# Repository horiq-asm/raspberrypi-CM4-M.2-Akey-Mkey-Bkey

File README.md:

boot CM5 via NVMe behind PCIe switch !!!<br>
新たに入手したCM5を入れるとNVMeからbootできました。
2024年12月クリスマスプレゼントです。<br>
youtube で動作画像ご覧ください　https://youtu.be/MDhNWYu6bRE

# raspberrypi-CM4-M.2-Akey-Mkey-Bkey
raspberypi　CM4にpcie swich を載せてM.2基板を複数動作できる基板を作成しました。
wifi6　１G　2.5Gのnicが動きます。
MkeyにはNVMeを搭載しています。

$ lspci<br>
00:00.0 PCI bridge: Broadcom Inc. and subsidiaries BCM2711 PCIe Bridge (rev 20)<br>
01:00.0 PCI bridge: ASMedia Technology Inc. ASM1184e 4-Port PCIe x1 Gen2 Packet Switch<br>
02:01.0 PCI bridge: ASMedia Technology Inc. ASM1184e 4-Port PCIe x1 Gen2 Packet Switch<br>
02:03.0 PCI bridge: ASMedia Technology Inc. ASM1184e 4-Port PCIe x1 Gen2 Packet Switch<br>
02:05.0 PCI bridge: ASMedia Technology Inc. ASM1184e 4-Port PCIe x1 Gen2 Packet Switch<br>
02:07.0 PCI bridge: ASMedia Technology Inc. ASM1184e 4-Port PCIe x1 Gen2 Packet Switch<br>
03:00.0 Network controller: MEDIATEK Corp. MT7921 802.11ax PCI Express Wireless Network Adapter<br>
04:00.0 Non-Volatile memory controller: KIOXIA Corporation NVMe SSD (rev 01)<br>
05:00.0 Ethernet controller: Intel Corporation Ethernet Controller I226-V (rev 04)<br>
<br>
$ ethtool eth1<br>
Settings for eth1:<br>
        Supported ports: [ TP ]<br>
        Supported link modes:   10baseT/Half 10baseT/Full<br>
                                100baseT/Half 100baseT/Full<br>
                                1000baseT/Full<br>
                                2500baseT/Full<br>
        Supported pause frame use: Symmetric<br>
        Supports auto-negotiation: Yes<br>
        Supported FEC modes: Not reported<br>
        Advertised link modes:  10baseT/Half 10baseT/Full<br>
                                100baseT/Half 100baseT/Full<br>
                                1000baseT/Full<br>
                                2500baseT/Full<br>
        Advertised pause frame use: Symmetric<br>
        Advertised auto-negotiation: Yes<br>
        Advertised FEC modes: Not reported<br>
        Speed: 2500Mb/s<br>
        Duplex: Full<br>
        Auto-negotiation: on<br>
        Port: Twisted Pair<br>
        PHYAD: 0<br>
        Transceiver: internal<br>
        MDI-X: off (auto)<br>
netlink error: Operation not permitted<br>
        Current message level: 0x00000007 (7)<br>
                               drv probe link<br>
        Link detected: yes<br>
<br>
<br>
$ nmcli d s<br>
DEVICE         TYPE      STATE                   CONNECTION<br>
wlan0          wifi      connected               WIFI_AP<br>
eth1           ethernet  connected               Wired connection 2<br>
lo             loopback  connected (externally)  lo<br>
p2p-dev-wlan0  wifi-p2p  disconnected            --<br>
eth0           ethernet  unavailable             --<br>
<br>
%%%<br>
Network controller: MEDIATEK Corp. MT7921 802.11ax PCI Express Wireless Network Adapter<br>
のためには　　/boot/firmware/config.txt　　に下記の変更が必要です。<br>
[all]<br>
dtparam=pciex1<br>
dtoverlay=pcie-32bit-dma<br>
<br>
<br>
$ iw phy0 info<br>
Wiphy phy0<br>
        wiphy index: 0<br>
        max # scan SSIDs: 4<br>
        max scan IEs length: 482 bytes<br>
        max # sched scan SSIDs: 10<br>
        max # match sets: 16<br>
        Retry short limit: 7<br>
        Retry long limit: 4<br>
        Coverage class: 0 (up to 0m)<br>
        Device supports AP-side u-APSD.<br>
        Device supports T-DLS.<br>
        Supported Ciphers:<br>
                * WEP40 (00-0f-ac:1)<br>
                * WEP104 (00-0f-ac:5)<br>
                * TKIP (00-0f-ac:2)<br>
                * CCMP-128 (00-0f-ac:4)<br>
                * CCMP-256 (00-0f-ac:10)<br>
                * GCMP-128 (00-0f-ac:8)<br>
                * GCMP-256 (00-0f-ac:9)<br>
                * CMAC (00-0f-ac:6)<br>
                * CMAC-256 (00-0f-ac:13)<br>
                * GMAC-128 (00-0f-ac:11)<br>
                * GMAC-256 (00-0f-ac:12)<br>
        Available Antennas: TX 0x3 RX 0x3<br>
        Configured Antennas: TX 0x3 RX 0x3<br>
        Supported interface modes:<br>
                 * managed<br>
                 * AP<br>
                 * AP/VLAN<br>
                 * monitor<br>
                 * P2P-client<br>
                 * P2P-GO<br>
        Band 1:<br>
                Capabilities: 0x9ff<br>
                        RX LDPC<br>
                        HT20/HT40<br>
                        SM Power Save disabled<br>
                        RX Greenfield<br>
                        RX HT20 SGI<br>
                        RX HT40 SGI<br>
                        TX STBC<br>
                        RX STBC 1-stream<br>
                        Max AMSDU length: 7935 bytes<br>
                        No DSSS/CCK HT40<br>
                Maximum RX AMPDU length 65535 bytes (exponent: 0x003)<br>
                Minimum RX AMPDU time spacing: No restriction (0x00)<br>
                HT TX/RX MCS rate indexes supported: 0-15<br>
                HE Iftypes: managed<br>
                        HE MAC Capabilities (0x08011a000040):<br>
                                +HTC HE Supported<br>
                                Trigger Frame MAC Padding Duration: 2<br>
                                OM Control<br>
                                Maximum A-MPDU Length Exponent: 3<br>
                                A-MSDU in A-MPDU<br>
                        HE PHY Capabilities: (0x2270ce120dc0b306423f00):<br>
                                HE40/2.4GHz<br>
                                242 tone RUs/2.4GHz<br>
                                Device Class: 1<br>
                                LDPC Coding in Payload<br>
                                HE SU PPDU with 1x HE-LTF and 0.8us GI<br>
                                NDP with 4x HE-LTF and 3.2us GI<br>
                                STBC Tx <= 80MHz<br>
                                STBC Rx <= 80MHz<br>
                                Full Bandwidth UL MU-MIMO<br>
                                Partial Bandwidth UL MU-MIMO<br>
                                DCM Max Constellation: 2<br>
                                DCM Max Constellation Rx: 2<br>
                                SU Beamformee<br>
                                Beamformee STS <= 80Mhz: 3<br>
                                Ng = 16 SU Feedback<br>
                                Ng = 16 MU Feedback<br>
                                Codebook Size SU Feedback<br>
                                Codebook Size MU Feedback<br>
                                Triggered CQI Feedback<br>
                                Partial Bandwidth Extended Range<br>
                                PPE Threshold Present<br>
                                Power Boost Factor ar<br>
                                HE SU PPDU & HE PPDU 4x HE-LTF 0.8us GI<br>
                                20MHz in 40MHz HE PPDU 2.4GHz<br>
                                DCM Max BW: 1<br>
                                Longer Than 16HE SIG-B OFDM Symbols<br>
                                Non-Triggered CQI Feedback<br>
                                TX 1024-QAM<br>
                                RX 1024-QAM<br>
                                RX Full BW SU Using HE MU PPDU with Compression SIGB<br>
                                RX Full BW SU Using HE MU PPDU with Non-Compression SIGB<br>
                        HE RX MCS and NSS set <= 80 MHz<br>
                                1 streams: MCS 0-11<br>
                                2 streams: MCS 0-11<br>
                                3 streams: not supported<br>
                                4 streams: not supported<br>
                                5 streams: not supported<br>
                                6 streams: not supported<br>
                                7 streams: not supported<br>
                                8 streams: not supported<br>
                        HE TX MCS and NSS set <= 80 MHz<br>
                                1 streams: MCS 0-11<br>
                                2 streams: MCS 0-11<br>
                                3 streams: not supported<br>
                                4 streams: not supported<br>
                                5 streams: not supported<br>
                                6 streams: not supported<br>
                                7 streams: not supported<br>
                                8 streams: not supported<br>
                        PPE Threshold 0x39 0x1c 0xc7 0x71 0x1c 0x07<br>
                EHT Iftypes: managed<br>
                        EHT MAC Capabilities (0x0000):<br>
                        EHT PHY Capabilities: (0x0000000000000000):<br>
                        EHT MCS/NSS: (0x):<br>
                        EHT bw=20 MHz, max NSS for MCS 0-7: Rx=0, Tx=0<br>
                        EHT bw=20 MHz, max NSS for MCS 8-9: Rx=0, Tx=0<br>
                        EHT bw=20 MHz, max NSS for MCS 10-11: Rx=0, Tx=0<br>
                        EHT bw=20 MHz, max NSS for MCS 12-13: Rx=0, Tx=0<br>
                HE Iftypes: AP<br>
                        HE MAC Capabilities (0x00011a081044):<br>
                                +HTC HE Supported<br>
                                BSR<br>
                                OM Control<br>
                                Maximum A-MPDU Length Exponent: 3<br>
                                BQR<br>
                                A-MSDU in A-MPDU<br>
                                OM Control UL MU Data Disable RX<br>
                        HE PHY Capabilities: (0x0220ce120000a000000c00):<br>
                                HE40/2.4GHz<br>
                                LDPC Coding in Payload<br>
                                NDP with 4x HE-LTF and 3.2us GI<br>
                                STBC Tx <= 80MHz<br>
                                STBC Rx <= 80MHz<br>
                                Full Bandwidth UL MU-MIMO<br>
                                Partial Bandwidth UL MU-MIMO<br>
                                DCM Max Constellation: 2<br>
                                DCM Max Constellation Rx: 2<br>
                                Partial Bandwidth Extended Range<br>
                                PPE Threshold Present<br>
                                TX 1024-QAM<br>
                                RX 1024-QAM<br>
                        HE RX MCS and NSS set <= 80 MHz<br>
                                1 streams: MCS 0-11<br>
                                2 streams: MCS 0-11<br>
                                3 streams: not supported<br>
                                4 streams: not supported<br>
                                5 streams: not supported<br>
                                6 streams: not supported<br>
                                7 streams: not supported<br>
                                8 streams: not supported<br>
                        HE TX MCS and NSS set <= 80 MHz<br>
                                1 streams: MCS 0-11<br>
                                2 streams: MCS 0-11<br>
                                3 streams: not supported<br>
                                4 streams: not supported<br>
                                5 streams: not supported<br>
                                6 streams: not supported<br>
                                7 streams: not supported<br>
                                8 streams: not supported<br>
                        PPE Threshold 0x39 0x1c 0xc7 0x71 0x1c 0x07<br>
                EHT Iftypes: AP<br>
                        EHT MAC Capabilities (0x0000):<br>
                        EHT PHY Capabilities: (0x0000000000000000):<br>
                        EHT MCS/NSS: (0x):<br>
                        EHT bw=20 MHz, max NSS for MCS 0-7: Rx=0, Tx=0<br>
                        EHT bw=20 MHz, max NSS for MCS 8-9: Rx=0, Tx=0<br>
                        EHT bw=20 MHz, max NSS for MCS 10-11: Rx=0, Tx=0<br>
                        EHT bw=20 MHz, max NSS for MCS 12-13: Rx=0, Tx=0<br>
                Bitrates (non-HT):<br>
                        * 1.0 Mbps (short preamble supported)<br>
                        * 2.0 Mbps (short preamble supported)<br>
                        * 5.5 Mbps (short preamble supported)<br>
                        * 11.0 Mbps (short preamble supported)<br>
                        * 6.0 Mbps<br>
                        * 9.0 Mbps<br>
                        * 12.0 Mbps<br>
                        * 18.0 Mbps<br>
                        * 24.0 Mbps<br>
                        * 36.0 Mbps<br>
                        * 48.0 Mbps<br>
                        * 54.0 Mbps<br>
                Frequencies:<br>
                        * 2412 MHz [1] (20.0 dBm)<br>
                        * 2417 MHz [2] (20.0 dBm)<br>
                        * 2422 MHz [3] (20.0 dBm)<br>
                        * 2427 MHz [4] (20.0 dBm)<br>
                        * 2432 MHz [5] (20.0 dBm)<br>
                        * 2437 MHz [6] (20.0 dBm)<br>
                        * 2442 MHz [7] (20.0 dBm)<br>
                        * 2447 MHz [8] (20.0 dBm)<br>
                        * 2452 MHz [9] (20.0 dBm)<br>
                        * 2457 MHz [10] (20.0 dBm)<br>
                        * 2462 MHz [11] (20.0 dBm)<br>
                        * 2467 MHz [12] (20.0 dBm)<br>
                        * 2472 MHz [13] (20.0 dBm)<br>
                        * 2484 MHz [14] (20.0 dBm)<br>
        Band 2:<br>
                Capabilities: 0x9ff<br>
                        RX LDPC<br>
                        HT20/HT40<br>
                        SM Power Save disabled<br>
                        RX Greenfield<br>
                        RX HT20 SGI<br>
                        RX HT40 SGI<br>
                        TX STBC<br>
                        RX STBC 1-stream<br>
                        Max AMSDU length: 7935 bytes<br>
                        No DSSS/CCK HT40<br>
                Maximum RX AMPDU length 65535 bytes (exponent: 0x003)<br>
                Minimum RX AMPDU time spacing: No restriction (0x00)<br>
                HT TX/RX MCS rate indexes supported: 0-15<br>
                VHT Capabilities (0x339071b2):<br>
                        Max MPDU length: 11454<br>
                        Supported Channel Width: neither 160 nor 80+80<br>
                        RX LDPC<br>
                        short GI (80 MHz)<br>
                        TX STBC<br>
                        SU Beamformee<br>
                        MU Beamformee<br>
                        RX antenna pattern consistency<br>
                        TX antenna pattern consistency<br>
                VHT RX MCS set:<br>
                        1 streams: MCS 0-9<br>
                        2 streams: MCS 0-9<br>
                        3 streams: not supported<br>
                        4 streams: not supported<br>
                        5 streams: not supported<br>
                        6 streams: not supported<br>
                        7 streams: not supported<br>
                        8 streams: not supported<br>
                VHT RX highest supported: 0 Mbps<br>
                VHT TX MCS set:<br>
                        1 streams: MCS 0-9<br>
                        2 streams: MCS 0-9<br>
                        3 streams: not supported<br>
                        4 streams: not supported<br>
                        5 streams: not supported<br>
                        6 streams: not supported<br>
                        7 streams: not supported<br>
                        8 streams: not supported<br>
                VHT TX highest supported: 0 Mbps<br>
                VHT extended NSS: supported<br>
                HE Iftypes: managed<br>
                        HE MAC Capabilities (0x08011a000040):<br>
                                +HTC HE Supported<br>
                                Trigger Frame MAC Padding Duration: 2<br>
                                OM Control<br>
                                Maximum A-MPDU Length Exponent: 3<br>
                                A-MSDU in A-MPDU<br>
                        HE PHY Capabilities: (0x4470ce120dc0b306423f00):<br>
                                HE40/HE80/5GHz<br>
                                242 tone RUs/5GHz<br>
                                Device Class: 1<br>
                                LDPC Coding in Payload<br>
                                HE SU PPDU with 1x HE-LTF and 0.8us GI<br>
                                NDP with 4x HE-LTF and 3.2us GI<br>
                                STBC Tx <= 80MHz<br>
                                STBC Rx <= 80MHz<br>
                                Full Bandwidth UL MU-MIMO<br>
                                Partial Bandwidth UL MU-MIMO<br>
                                DCM Max Constellation: 2<br>
                                DCM Max Constellation Rx: 2<br>
                                SU Beamformee<br>
                                Beamformee STS <= 80Mhz: 3<br>
                                Ng = 16 SU Feedback<br>
                                Ng = 16 MU Feedback<br>
                                Codebook Size SU Feedback<br>
                                Codebook Size MU Feedback<br>
                                Triggered CQI Feedback<br>
                                Partial Bandwidth Extended Range<br>
                                PPE Threshold Present<br>
                                Power Boost Factor ar<br>
                                HE SU PPDU & HE PPDU 4x HE-LTF 0.8us GI<br>
                                20MHz in 40MHz HE PPDU 2.4GHz<br>
                                DCM Max BW: 1<br>
                                Longer Than 16HE SIG-B OFDM Symbols<br>
                                Non-Triggered CQI Feedback<br>
                                TX 1024-QAM<br>
                                RX 1024-QAM<br>
                                RX Full BW SU Using HE MU PPDU with Compression SIGB<br>
                                RX Full BW SU Using HE MU PPDU with Non-Compression SIGB<br>
                        HE RX MCS and NSS set <= 80 MHz<br>
                                1 streams: MCS 0-11<br>
                                2 streams: MCS 0-11<br>
                                3 streams: not supported<br>
                                4 streams: not supported<br>
                                5 streams: not supported<br>
                                6 streams: not supported<br>
                                7 streams: not supported<br>
                                8 streams: not supported<br>
                        HE TX MCS and NSS set <= 80 MHz<br>
                                1 streams: MCS 0-11<br>
                                2 streams: MCS 0-11<br>
                                3 streams: not supported<br>
                                4 streams: not supported<br>
                                5 streams: not supported<br>
                                6 streams: not supported<br>
                                7 streams: not supported<br>
                                8 streams: not supported<br>
                        PPE Threshold 0x39 0x1c 0xc7 0x71 0x1c 0x07<br>
                EHT Iftypes: managed<br>
                        EHT MAC Capabilities (0x0000):<br>
                        EHT PHY Capabilities: (0x0000000000000000):<br>
                        EHT MCS/NSS: (0x):<br>
                        EHT bw <= 80 MHz, max NSS for MCS 8-9: Rx=0, Tx=0<br>
                        EHT bw <= 80 MHz, max NSS for MCS 10-11: Rx=0, Tx=0<br>
                        EHT bw <= 80 MHz, max NSS for MCS 12-13: Rx=0, Tx=0<br>
                HE Iftypes: AP<br>
                        HE MAC Capabilities (0x00011a081044):<br>
                                +HTC HE Supported<br>
                                BSR<br>
                                OM Control<br>
                                Maximum A-MPDU Length Exponent: 3<br>
                                BQR<br>
                                A-MSDU in A-MPDU<br>
                                OM Control UL MU Data Disable RX<br>
                        HE PHY Capabilities: (0x0420ce120000a000000c00):<br>
                                HE40/HE80/5GHz<br>
                                LDPC Coding in Payload<br>
                                NDP with 4x HE-LTF and 3.2us GI<br>
                                STBC Tx <= 80MHz<br>
                                STBC Rx <= 80MHz<br>
                                Full Bandwidth UL MU-MIMO<br>
                                Partial Bandwidth UL MU-MIMO<br>
                                DCM Max Constellation: 2<br>
                                DCM Max Constellation Rx: 2<br>
                                Partial Bandwidth Extended Range<br>
                                PPE Threshold Present<br>
                                TX 1024-QAM<br>
                                RX 1024-QAM<br>
                        HE RX MCS and NSS set <= 80 MHz<br>
                                1 streams: MCS 0-11<br>
                                2 streams: MCS 0-11<br>
                                3 streams: not supported<br>
                                4 streams: not supported<br>
                                5 streams: not supported<br>
                                6 streams: not supported<br>
                                7 streams: not supported<br>
                                8 streams: not supported<br>
                        HE TX MCS and NSS set <= 80 MHz<br>
                                1 streams: MCS 0-11<br>
                                2 streams: MCS 0-11<br>
                                3 streams: not supported<br>
                                4 streams: not supported<br>
                                5 streams: not supported<br>
                                6 streams: not supported<br>
                                7 streams: not supported<br>
                                8 streams: not supported<br>
                        PPE Threshold 0x39 0x1c 0xc7 0x71 0x1c 0x07<br>
                EHT Iftypes: AP<br>
                        EHT MAC Capabilities (0x0000):<br>
                        EHT PHY Capabilities: (0x0000000000000000):<br>
                        EHT MCS/NSS: (0x):<br>
                        EHT bw <= 80 MHz, max NSS for MCS 8-9: Rx=0, Tx=0<br>
                        EHT bw <= 80 MHz, max NSS for MCS 10-11: Rx=0, Tx=0<br>
                        EHT bw <= 80 MHz, max NSS for MCS 12-13: Rx=0, Tx=0<br>
                Bitrates (non-HT):<br>
                        * 6.0 Mbps<br>
                        * 9.0 Mbps<br>
                        * 12.0 Mbps<br>
                        * 18.0 Mbps<br>
                        * 24.0 Mbps<br>
                        * 36.0 Mbps<br>
                        * 48.0 Mbps<br>
                        * 54.0 Mbps<br>
                Frequencies:<br>
                        * 5180 MHz [36] (20.0 dBm)<br>
                        * 5200 MHz [40] (20.0 dBm)<br>
                        * 5220 MHz [44] (20.0 dBm)<br>
                        * 5240 MHz [48] (20.0 dBm)<br>
                        * 5260 MHz [52] (20.0 dBm) (radar detection)<br>
                        * 5280 MHz [56] (20.0 dBm) (radar detection)<br>
                        * 5300 MHz [60] (20.0 dBm) (radar detection)<br>
                        * 5320 MHz [64] (20.0 dBm) (radar detection)<br>
                        * 5500 MHz [100] (23.0 dBm) (radar detection)<br>
                        * 5520 MHz [104] (23.0 dBm) (radar detection)<br>
                        * 5540 MHz [108] (23.0 dBm) (radar detection)<br>
                        * 5560 MHz [112] (23.0 dBm) (radar detection)<br>
                        * 5580 MHz [116] (23.0 dBm) (radar detection)<br>
                        * 5600 MHz [120] (23.0 dBm) (radar detection)<br>
                        * 5620 MHz [124] (23.0 dBm) (radar detection)<br>
                        * 5640 MHz [128] (23.0 dBm) (radar detection)<br>
                        * 5660 MHz [132] (23.0 dBm) (radar detection)<br>
                        * 5680 MHz [136] (23.0 dBm) (radar detection)<br>
                        * 5700 MHz [140] (23.0 dBm) (radar detection)<br>
                        * 5720 MHz [144] (disabled)<br>
                        * 5745 MHz [149] (disabled)<br>
                        * 5765 MHz [153] (disabled)<br>
                        * 5785 MHz [157] (disabled)<br>
                        * 5805 MHz [161] (disabled)<br>
                        * 5825 MHz [165] (disabled)<br>
                        * 5845 MHz [169] (disabled)<br>
                        * 5865 MHz [173] (disabled)<br>
                        * 5885 MHz [177] (disabled)<br>
        Supported commands:<br>
                 * new_interface<br>
                 * set_interface<br>
                 * new_key<br>
                 * start_ap<br>
                 * new_station<br>
                 * new_mpath<br>
                 * set_mesh_config<br>
                 * set_bss<br>
                 * authenticate<br>
                 * associate<br>
                 * deauthenticate<br>
                 * disassociate<br>
                 * join_ibss<br>
                 * join_mesh<br>
                 * remain_on_channel<br>
                 * set_tx_bitrate_mask<br>
                 * frame<br>
                 * frame_wait_cancel<br>
                 * set_wiphy_netns<br>
                 * set_channel<br>
                 * tdls_mgmt<br>
                 * tdls_oper<br>
                 * start_sched_scan<br>
                 * probe_client<br>
                 * set_noack_map<br>
                 * register_beacons<br>
                 * start_p2p_device<br>
                 * set_mcast_rate<br>
                 * connect<br>
                 * disconnect<br>
                 * channel_switch<br>
                 * set_qos_map<br>
                 * set_multicast_to_unicast<br>
                 * set_sar_specs<br>
        WoWLAN support:<br>
                 * wake up on disconnect<br>
                 * wake up on magic packet<br>
                 * wake up on pattern match, up to 1 patterns of 1-128 bytes,<br>
                   maximum packet offset 0 bytes<br>
                 * can do GTK rekeying<br>
                 * wake up on network detection, up to 10 match sets<br>
        software interface modes (can always be added):<br>
                 * AP/VLAN<br>
                 * monitor<br>
        valid interface combinations:<br>
                 * #{ managed, P2P-client } <= 2, #{ AP, P2P-GO } <= 1,<br>
                   total <= 2, #channels <= 2<br>
        HT Capability overrides:<br>
                 * MCS: ff ff ff ff ff ff ff ff ff ff<br>
                 * maximum A-MSDU length<br>
                 * supported channel width<br>
                 * short GI for 40 MHz<br>
                 * max A-MPDU length exponent<br>
                 * min MPDU start spacing<br>
        Device supports TX status socket option.<br>
        Device supports HT-IBSS.<br>
        Device supports SAE with AUTHENTICATE command<br>
        Device supports scan flush.<br>
        Device supports per-vif TX power setting<br>
        Driver supports full state transitions for AP/GO clients<br>
        Driver supports a userspace MPM<br>
        Device supports active monitor (which will ACK incoming frames)<br>
        Driver/device bandwidth changes during BSS lifetime (AP/GO mode)<br>
        Device supports configuring vdev MAC-addr on create.<br>
        Device supports randomizing MAC-addr in scans.<br>
        Device supports randomizing MAC-addr in sched scans.<br>
        max # scan plans: 1<br>
        max scan plan interval: 65535<br>
        max scan plan iterations: 0<br>
        Supported TX frame types:<br>
                 * IBSS: 0x00 0x10 0x20 0x30 0x40 0x50 0x60 0x70 0x80 0x90 0xa0 0xb0 0xc0 0xd0 0xe0 0xf0<br>
                 * managed: 0x00 0x10 0x20 0x30 0x40 0x50 0x60 0x70 0x80 0x90 0xa0 0xb0 0xc0 0xd0 0xe0 0xf0<br>
                 * AP: 0x00 0x10 0x20 0x30 0x40 0x50 0x60 0x70 0x80 0x90 0xa0 0xb0 0xc0 0xd0 0xe0 0xf0<br>
                 * AP/VLAN: 0x00 0x10 0x20 0x30 0x40 0x50 0x60 0x70 0x80 0x90 0xa0 0xb0 0xc0 0xd0 0xe0 0xf0<br>
                 * mesh point: 0x00 0x10 0x20 0x30 0x40 0x50 0x60 0x70 0x80 0x90 0xa0 0xb0 0xc0 0xd0 0xe0 0xf0<br>
                 * P2P-client: 0x00 0x10 0x20 0x30 0x40 0x50 0x60 0x70 0x80 0x90 0xa0 0xb0 0xc0 0xd0 0xe0 0xf0<br>
                 * P2P-GO: 0x00 0x10 0x20 0x30 0x40 0x50 0x60 0x70 0x80 0x90 0xa0 0xb0 0xc0 0xd0 0xe0 0xf0<br>
                 * P2P-device: 0x00 0x10 0x20 0x30 0x40 0x50 0x60 0x70 0x80 0x90 0xa0 0xb0 0xc0 0xd0 0xe0 0xf0<br>
        Supported RX frame types:<br>
                 * IBSS: 0x40 0xb0 0xc0 0xd0<br>
                 * managed: 0x40 0xb0 0xd0<br>
                 * AP: 0x00 0x20 0x40 0xa0 0xb0 0xc0 0xd0<br>
                 * AP/VLAN: 0x00 0x20 0x40 0xa0 0xb0 0xc0 0xd0<br>
                 * mesh point: 0xb0 0xc0 0xd0<br>
                 * P2P-client: 0x40 0xd0<br>
                 * P2P-GO: 0x00 0x20 0x40 0xa0 0xb0 0xc0 0xd0<br>
                 * P2P-device: 0x40 0xd0<br>
        Supported extended features:<br>
                * [ RRM ]: RRM<br>
                * [ SET_SCAN_DWELL ]: scan dwell setting<br>
                * [ BEACON_RATE_LEGACY ]: legacy beacon rate setting<br>
                * [ BEACON_RATE_HT ]: HT beacon rate setting<br>
                * [ BEACON_RATE_VHT ]: VHT beacon rate setting<br>
                * [ FILS_STA ]: STA FILS (Fast Initial Link Setup)<br>
                * [ CQM_RSSI_LIST ]: multiple CQM_RSSI_THOLD records<br>
                * [ CONTROL_PORT_OVER_NL80211 ]: control port over nl80211<br>
                * [ ACK_SIGNAL_SUPPORT ]: ack signal level support<br>
                * [ TXQS ]: FQ-CoDel-enabled intermediate TXQs<br>
                * [ CAN_REPLACE_PTK0 ]: can safely replace PTK 0 when rekeying<br>
                * [ AIRTIME_FAIRNESS ]: airtime fairness scheduling<br>
                * [ AQL ]: Airtime Queue Limits (AQL)<br>
                * [ CONTROL_PORT_NO_PREAUTH ]: disable pre-auth over nl80211 control port support<br>
                * [ SCAN_FREQ_KHZ ]: scan on kHz frequency support<br>
                * [ CONTROL_PORT_OVER_NL80211_TX_STATUS ]: tx status for nl80211 control port support<br>
                * [ BEACON_RATE_HE ]: HE beacon rate support (AP/mesh)<br>

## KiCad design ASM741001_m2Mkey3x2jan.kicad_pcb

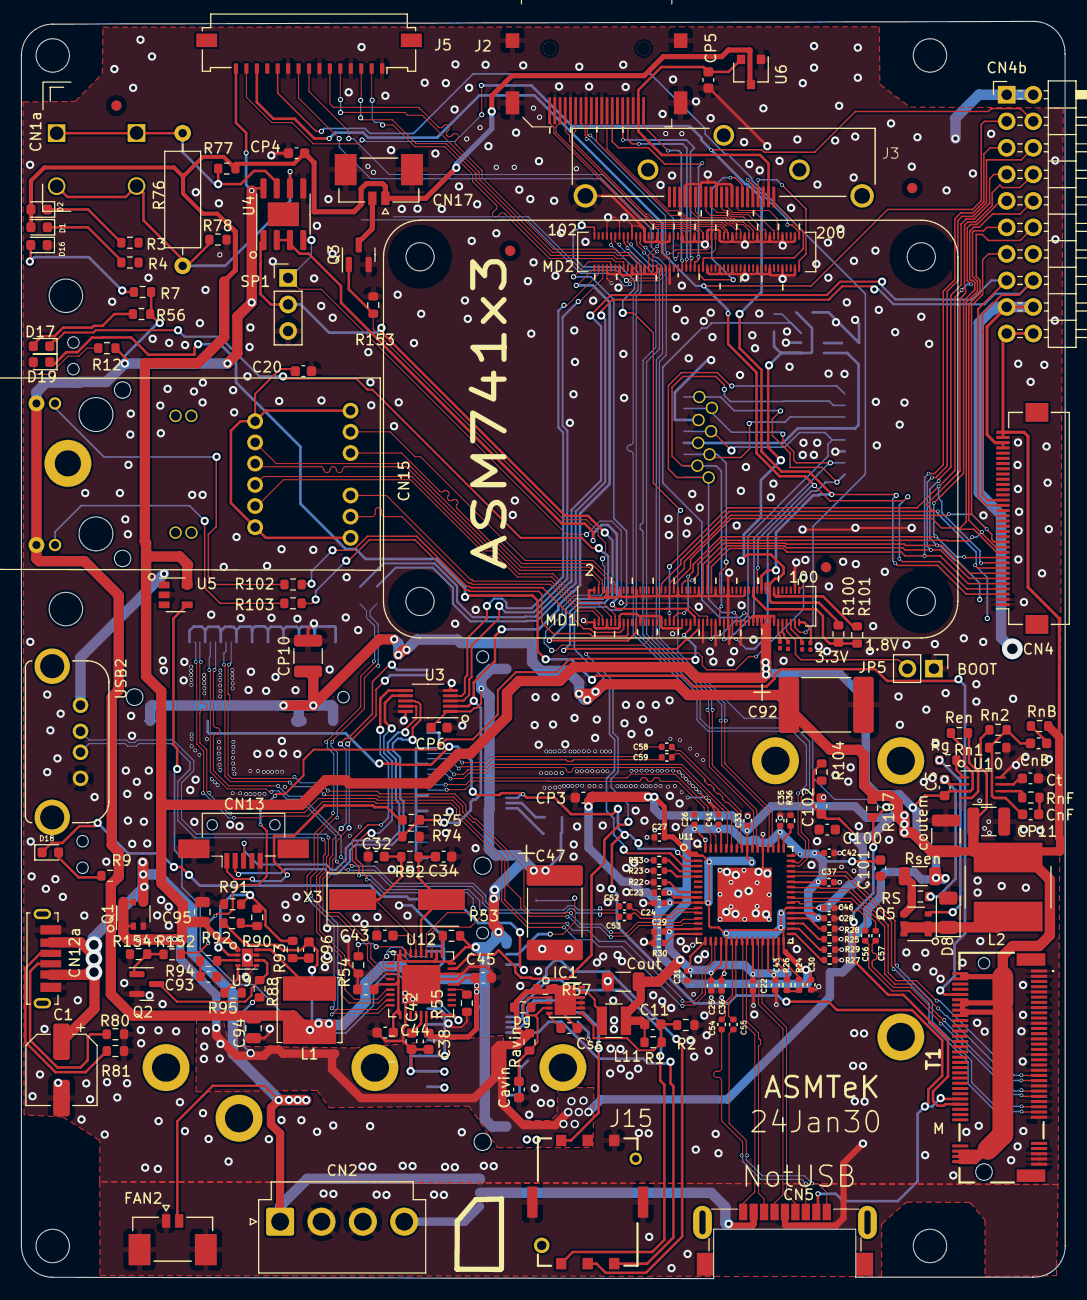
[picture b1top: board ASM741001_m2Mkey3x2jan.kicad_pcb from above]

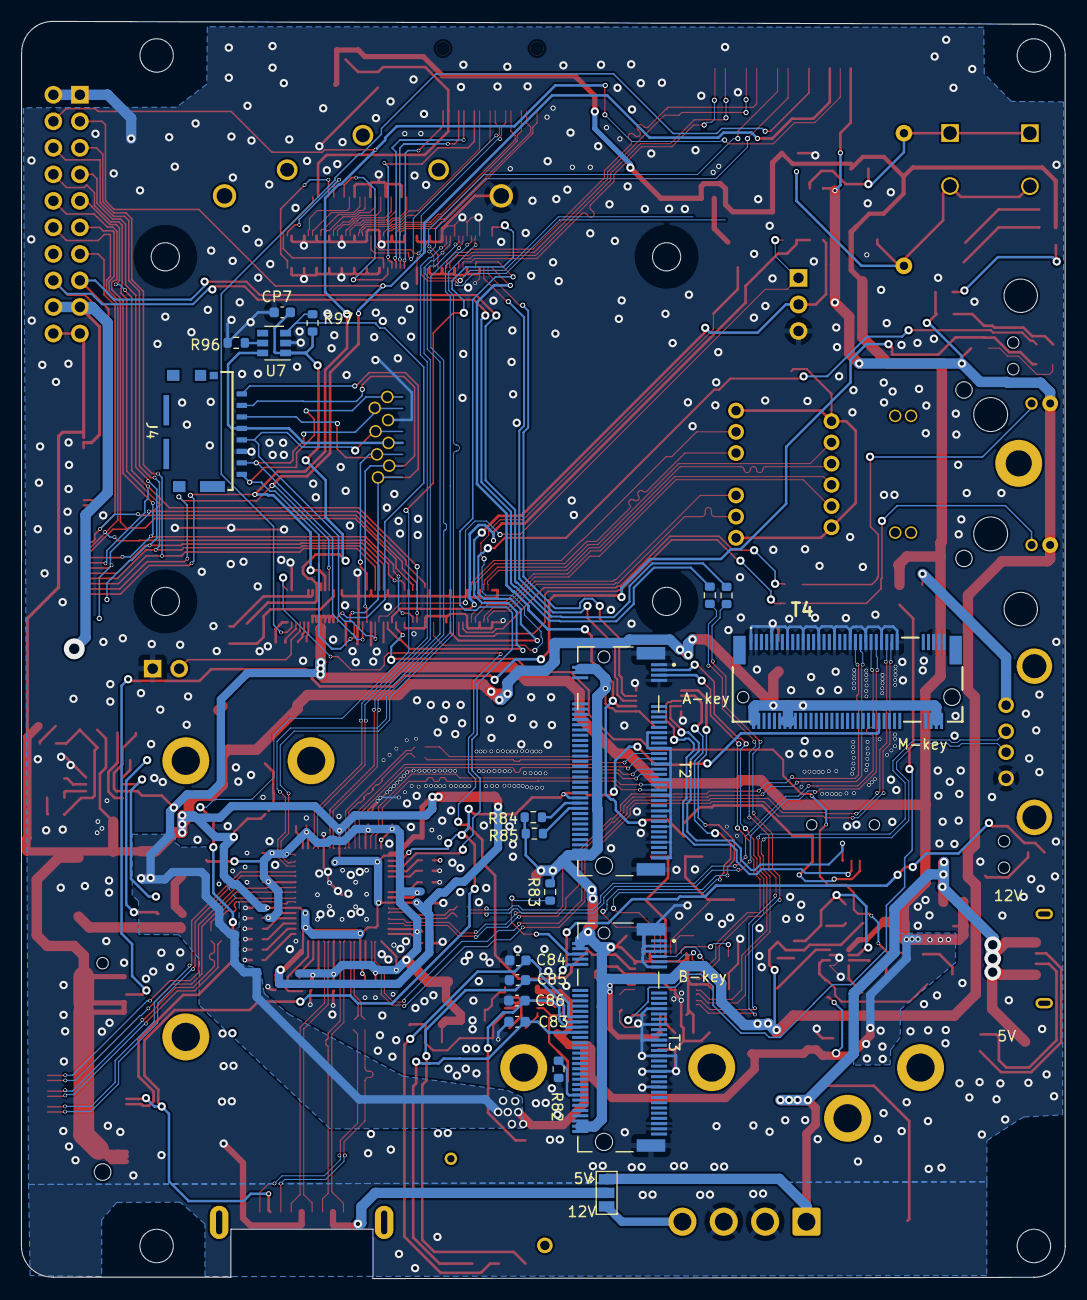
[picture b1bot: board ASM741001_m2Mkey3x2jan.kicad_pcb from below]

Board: 2 copper layers, 100.0 x 120.4 mm, 192 parts (18 on the bottom side), 211 nets.

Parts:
C1: RSA0J331MCN1GS; CP_Elec_6.3x5.8
C2, C42#2, C43, C44, C45: 104; C_0603_1608Metric
C11: 25p; C_0603_1608Metric
C20: 0.1u/25v; C_0603_1608Metric
C22, C23, C24, C25, C26, C27, C28, C29, C30, C31, C33, C35, C36, C37, C41, C42, C43#2, C46, C52, C53, C54, C55, C56, C57, C58, C59: 100nF; C_0402_1005Metric
C32, C34, C96: 15ｐ; C_0603_1608Metric
C38: 4.7u; C_0603_1608Metric
C47, C92: ECASD40J476M025K00; C_2220_5650Metric_Pad1.97x5.40mm_HandSolder
C83, C84, C85, C86: C:2; C_0603_1608Metric
C93: 10ｐ; C_0603_1608Metric
C94, C95: GRM188R61C106MAALD; C_0805_2012Metric
C100, C102: C_0603_1608Metric
C101: 100n; C_0603_1608Metric
CN1a: TB411-2-2-E-1; PinHeader_1x02_P2.54mm_Vertical
CN2: JST_VH_B4P-VH_1x04_P3.96mm_Vertical
CN4: CN:27; Hirose_FH12-34S-0.5SH_1x34-1MP_P0.50mm_Horizontal
CN4b: PinHeader_2x10_P2.54mm_Horizontal
CN5: USB_A_Female_AU-Y1006-3
CN12a: CUI_UJC-VP-3-SMT-TR
CN13: CN:5; USB_Mini-B_AdamTech_MUSB-B5-S-VT-TSMT-1_SMD_Vertical
CN15: 0838-1x1t-w7
CN17: MOLEX_533980271
CP3, CP4, CP5, CP6, CP7: 104; C_0603_1608Metric
CP10, CP11: C_1210_3225Metric
CS: 22n; C_0603_1608Metric
Cavin: 10n; C_0603_1608Metric
CnB: 220p; C_0603_1608Metric
CnF: 2.2n; C_0603_1608Metric
Cout: 22u; C_1206_3216Metric
Css: 470p; C_0603_1608Metric
Ct: 1n; C_0603_1608Metric
D1, D16: green; LED_0603_1608Metric
D2, D17: red; LED_0603_1608Metric
D8: D_1206_3216Metric
D18: blue; LED_0603_1608Metric
D19: yelow; LED_0603_1608Metric
FAN2: MOLEX_533980271
IC1: RP510L00; DFN-12-1EP_3x3mm_P0.5mm_EP2.05x2.86mm
J2: HDMI_A_Female_2000-1-2-41-00-BK; HDMI
J3: SS-53000-003; BEL_SS-53000-003
J4: 105162-0001
J5: 0522711579; Molex_200528-0150_1x15-1MP_P1.00mm_Horizontal
J15: GCT_SIM8051-6-0-14-01-X-REVD
JP1, JP2, JP3, JP4: nf; R_0201_0603Metric
JP5: PinHeader_1x02_P2.54mm_Vertical
L1: SRN6045TA-4R7M; L_Bourns_SRN6045TA
L2: SRN6045TA-4R7M; L_Bourns_SRN8040TA
L11: 1u; L_Abracon_ASPI-3012S
Module1: ComputeModule4; Raspberry-Pi-4-Compute-Module
Q1, Q5: SSM6J808R; TSOP-6_1.65x3.05mm_P0.95mm
Q2, Q3: BSS138-TP; SOT-23
R1, R2: 20k; R_0603_1608Metric
R3, R4, R9, R12, R56, R77, R78, R82, R153: 1k; R_0603_1608Metric
R7: 4.7k; R_0603_1608Metric
R22, R23, R25, R27: 1K; R_0402_1005Metric
R24, R26, R28, R29, R33: 10K; R_0402_1005Metric
R30, R36: 12.1K; R_0402_1005Metric
R52: 1M; R_0603_1608Metric
R53, R55, R57: 51k; R_0603_1608Metric
R54, R91: 12k; R_0603_1608Metric
R74, R75, R88: 2.2k; R_0603_1608Metric
R76: 680 1/2w; R_Axial_DIN0309_L9.0mm_D3.2mm_P12.70mm_Horizontal
R80, R81, R95: 5.1k; R_0603_1608Metric
R83, R84, R85, R94, R154: 10k; R_0603_1608Metric
R90: 3.9k; R_0603_1608Metric
R92: ERJ-3EKF5102V; R_0603_1608Metric
R93: 0k; R_0603_1608Metric
R96, R97: 2.2ｋ; R_0603_1608Metric
R100, R101: R:2; R_0603_1608Metric
R102, R103: 1ｋ; R_0603_1608Metric
R104: R_0603_1608Metric
R105x, R106x, R152: 0; R_0603_1608Metric
R107: 100k; R_0603_1608Metric
RS: 20; R_0603_1608Metric
Ravin: 1; R_0603_1608Metric
Ren: 10k; R_0603_1608Metric
Rg: 20; R_0603_1608Metric
Rn1: 10k; R_0603_1608Metric
Rn2: 30.9k; R_0603_1608Metric
RnB: 1k; R_0603_1608Metric
RnF: 8.2k; R_0603_1608Metric
Rsen: 27m; R_1206_3216Metric
SP1: PinHeader_1x03_P2.54mm_Vertical
T1: 1-2199230-5; MDT420M01001
T2: 2199230-8; b9973afb-34f9-4941-8c1f-dffebdb6dde0
T3: 2199230-3; b9973afb-34f9-4941-8c1f-dffebdb6dde0
T4: MDT420M01001
U3: FSUSB42MUX; MSOP-10-1EP_3x3mm_P0.5mm_EP1.68x1.88mm_ThermalVias
U4: THVD1419; SOIC-8-1EP_3.9x4.9mm_P1.27mm_EP2.29x3mm
U5: TPS2041C; SOT-23-5
U6: AP2331W; SC-59
U7: BD2222G; SOT-23-6
U9: NJW4122KU1-TE3; DFN-8-1EP_2x2mm_P0.5mm_EP1.05x1.75mm
U10: NJW4160R-TE2; SOT-23-8_Handsoldering
U11: ASM1184e; QFN-64-1EP_9x9mm_P0.5mm_EP5.2x5.2mm
U12: USB2514BI-AEZG-TR; QFN-36-1EP_6x6mm_P0.5mm_EP3.7x3.7mm
USB2: USB-A-S-X-X-VT
X3: 24M; Crystal_SMD_HC49-SD
coutem: C_1210_3225Metric
h2, h2#2, h2#3, h10, h15, h15#2: MountingHole_3.2mm_M3
h4, h4#2, h5, h5#2: MountingHole_1.1mm; MountingHole_2.1mm
pg: 100k; R_0603_1608Metric

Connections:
1.8V: Module1.88 (+1.8v_(Output)), Module1.90 (+1.8v_(Output)), R101.1
1v2: C11.2, C22.1, C23.1, C25.1, C26.1, C28.1, C29.1, C31.1, C35.1, C37.1, C41.1, C42.1, C43#2.1, C101.2, Cout.1, L11.2, R1.2, U11.9 (1V2), U11.15 (1V2), U11.17 (1V2), U11.20 (1V2), U11.26 (1V2), U11.29 (1V2), U11.37 (1V2), U11.43 (1V2), U11.48 (1V2), U11.50 (1V2), U11.61 (1V2), U11.64 (1V2)
3.3V: C2.1, C38.2, C44.1, C45.2, C47.2, C94.2, C96.1, CN15.18, CN15.20, CP6.1, J5.15, L1.1, R7.2, R9.1, R12.2, R53.1, R56.2, R83.2, R84.1, R85.1, R92.1, T2.2, T2.4, T2.72, T2.74, T3.2, T3.4, T3.70, T3.72, T3.74, U3.1, U4.8, U12.5, U12.10, U12.15, U12.23, U12.27, U12.29, U12.36
3.3vem: C24.1, C27.1, C30.1, C33.1, C36.1, C46.1, C92.1, C102.1, CN4.33, CN4.34, CN4b.19, CN4b.20, CP3.2, CP10.1, CP11.2, L2.2, R24.1, R26.1, R104.2, R107.2, Rn2.1, RnB.1, T1.2, T1.4, T1.12, T1.14, T1.16, T1.18, T1.70, T1.72, T1.74, T4.2, T4.4, T4.12, T4.14, T4.16, T4.18, T4.70, T4.72, T4.74, U11.1 (3V_AUX), U11.10 (3V3), U11.21 (3V3), U11.32 (3V3), U11.38 (3V3), U11.56 (3V3), coutem.1
5VIN: C1.1, CN2.1, CN12a.A9, CN12a.B9, FAN2.2, Q1.4
5VINb: CN4.31, CN4.32, CN4b.17, CN4b.18
A5: CN12a.A5, R81.1
B5: CN12a.B5, R80.1
BTEN: R84.2, T2.54
BT_nDisable: JP2.2, Module1.91 (BT_nDisable)
CAM1_C_N: J5.8, Module1.127 (CAM1_C_N)
CAM1_C_P: J5.9, Module1.129 (CAM1_C_P)
CAM1_D0_N: J5.2, Module1.115 (CAM1_D0_N)
CAM1_D0_P: J5.3, Module1.117 (CAM1_D0_P)
CAM1_D1_N: J5.5, Module1.121 (CAM1_D1_N)
CAM1_D1_P: J5.6, Module1.123 (CAM1_D1_P)
CRF: C42#2.1, U12.14
Camera_GPIO: J5.11, Module1.97 (Camera_GPIO)
Ethernet_Pair0_N: CN15.10, Module1.10 (Ethernet_Pair0_N)
Ethernet_Pair0_P: CN15.11, Module1.12 (Ethernet_Pair0_P)
Ethernet_Pair1_N: CN15.5, Module1.6 (Ethernet_Pair1_N)
Ethernet_Pair1_P: CN15.4, Module1.4 (Ethernet_Pair1_P)
Ethernet_Pair2_N: CN15.2, Module1.9 (Ethernet_Pair2_N)
Ethernet_Pair2_P: CN15.3, Module1.11 (Ethernet_Pair2_P)
Ethernet_Pair3_N: CN15.9, Module1.5 (Ethernet_Pair3_N)
Ethernet_Pair3_P: CN15.8, Module1.3 (Ethernet_Pair3_P)
Ethernet_nLED2: Module1.17 (Ethernet_nLED2(3.3v)), R103.1
Ethernet_nLED3: Module1.15 (Ethernet_nLED3(3.3v)), R102.1
Ethgreen: CN15.19, R102.2
Ethyell: CN15.17, R103.2
FAN: CN17.2, Q3.3
FB: R90.1, R91.1, R93.1, U9.2
FBR: R90.2, R92.2
GLOBAL_EN: JP4.2, Module1.99 (Global_EN)
GND: C1.2, C2.2, C20.2, C22.2, C23.2, C24.2, C25.2, C26.2, C27.2, C28.2, C29.2, C30.2, C31.2, C32.2, C33.2, C34.2, C35.2, C36.2, C37.2, C38.1, C41.2, C42.2, C42#2.2, C43.2, C43#2.2, C44.2, C45.1, C46.2, C47.1, C83.2, C84.2, C85.2, C86.2, C92.2, C93.2, C94.1, C95.1, C101.1, C102.2, CN2.2, CN2.3, CN4.1, CN4.2, CN4b.1, CN4b.2, CN5.7, CN12a.A12, CN12a.B12, CN13.5, CN13.6, CN17.S1, CN17.S2, CP3.1, CP4.2, CP5.1, CP6.2, CP7.2, CP10.2, CP11.1, Cavin.1, Cout.2, Css.1, Ct.2, D8.2, D16.1, FAN2.1, FAN2.S1, FAN2.S2, IC1.8, IC1.9, IC1.10, IC1.13, J2.2, J2.5, J2.8, J2.11, J2.17, J2.SH, J3.2, J3.5, J3.8, J3.11, J3.17, J3.S1, J4.6, J5.1, J5.4, J5.7, J5.10, J15.6, J15.10, J15.C5, JP5.1, Module1.1 (GND), Module1.2 (GND), Module1.7 (GND), Module1.8 (GND), Module1.13 (GND), Module1.14 (GND), Module1.22 (GND), Module1.23 (GND), Module1.32 (GND), Module1.33 (GND), Module1.42 (GND), Module1.43 (GND), Module1.52 (GND), Module1.53 (GND), Module1.59 (GND), Module1.60 (GND), Module1.65 (GND), Module1.66 (GND), Module1.71 (GND), Module1.74 (GND), Module1.98 (GND), Module1.107 (GND), Module1.108 (GND), Module1.113 (GND), Module1.114 (GND), Module1.119 (GND), Module1.120 (GND), Module1.125 (GND), Module1.126 (GND), Module1.131 (GND), Module1.132 (GND), Module1.137 (GND), Module1.138 (GND), Module1.144 (GND), Module1.150 (GND), Module1.155 (GND), Module1.156 (GND), Module1.161 (GND), Module1.162 (GND), Module1.167 (GND), Module1.168 (GND), Module1.173 (GND), Module1.174 (GND), Module1.179 (GND), Module1.180 (GND), Module1.185 (GND), Module1.186 (GND), Module1.191 (GND), Module1.192 (GND), Module1.197 (GND), Module1.198 (GND), Q1.3, Q2.2, Q3.2, R2.1, R22.2, R23.2, R25.2, R27.2, R28.1, R29.1, R30.2, R36.2, R54.2, R55.2, R57.1, R74.1, R78.1, R80.2, R81.2, R82.1, R91.2, R95.2, R96.1, R153.1, R154.1, Rn1.2, SP1.3, T1.1, T1.3, T1.9, T1.15, T1.21, T1.27, T1.33, T1.39, T1.45, T1.51, T1.57, T1.71, T1.73, T1.75, T2.1, T2.7, T2.27, T2.33, T2.39, T2.45, T2.51, T2.57, T2.63, T2.69, T2.75, T2.S1, T2.S2, T3.3, T3.5, T3.11, T3.27, T3.33, T3.39, T3.45, T3.51, T3.57, T3.71, T3.73, T3.S1, T3.S2, T4.1, T4.3, T4.9, T4.15, T4.21, T4.27, T4.33, T4.39, T4.45, T4.51, T4.57, T4.71, T4.73, T4.75, U3.5, U3.10, U4.5, U5.2, U6.1, U7.2, U9.5, U9.7, U9.9, U10.8, U11.53 (GND), U11.65 (GND), U12.11, U12.24, U12.25, U12.37, USB2.4, coutem.2
GPIO2: CN4.5, CN4b.5, Module1.58 (GPIO2)
GPIO3: CN4.6, CN4b.6, Module1.56 (GPIO3)
GPIO4: CN4.7, CN4b.7, Module1.54 (GPIO4)
GPIO5: CN4.8, CN4b.8, Module1.34 (GPIO5)
GPIO7: CN4.9, CN4b.9, Module1.37 (GPIO7)
GPIO8: CN4.10, CN4b.10, Module1.39 (GPIO8)
GPIO9: CN4.11, CN4b.11, Module1.40 (GPIO9)
GPIO10: CN4.12, CN4b.12, Module1.44 (GPIO10)
GPIO11: CN4.13, CN4b.13, Module1.38 (GPIO11)
GPIO14: Module1.55 (GPIO14), SP1.1, U4.4
GPIO15: Module1.51 (GPIO15), SP1.2, U4.1
GPIO16: Module1.29 (GPIO16), Q3.1, R153.2
GPIO18: Module1.49 (GPIO18), U4.2, U4.3
GPIO23: Module1.47 (GPIO23), R152.1
GPIO_VDD: Module1.78 (GPIO_VREF(1.8v/3.3v_Input)), R100.2, R101.2
H5V: CP5.2, J2.18, J3.18, U6.2
HDMI0_CEC: J3.13, Module1.151 (HDMI0_CEC)
HDMI0_CLK_N: J3.12, Module1.190 (HDMI0_CLK_N)
HDMI0_CLK_P: J3.10, Module1.188 (HDMI0_CLK_P)
HDMI0_HOTPLUG: J3.19, Module1.153 (HDMI0_HOTPLUG)
HDMI0_SCL: J3.15, Module1.200 (HDMI0_SCL)
HDMI0_SDA: J3.16, Module1.199 (HDMI0_SDA)
HDMI0_TX0_N: J3.9, Module1.184 (HDMI0_TX0_N)
HDMI0_TX0_P: J3.7, Module1.182 (HDMI0_TX0_P)
HDMI0_TX1_N: J3.6, Module1.178 (HDMI0_TX1_N)
HDMI0_TX1_P: J3.4, Module1.176 (HDMI0_TX1_P)
HDMI0_TX2_N: J3.3, Module1.172 (HDMI0_TX2_N)
HDMI0_TX2_P: J3.1, Module1.170 (HDMI0_TX2_P)
HDMI1_CEC: J2.13, Module1.149 (HDMI1_CEC)
HDMI1_CLK_N: J2.12, Module1.166 (HDMI1_CLK_N)
HDMI1_CLK_P: J2.10, Module1.164 (HDMI1_CLK_P)
HDMI1_HOTPLUG: J2.19, Module1.143 (HDMI1_HOTPLUG)
HDMI1_SCL: J2.15, Module1.147 (HDMI1_SCL)
HDMI1_SDA: J2.16, Module1.145 (HDMI1_SDA)
HDMI1_TX0_N: J2.9, Module1.160 (HDMI1_TX0_N)
HDMI1_TX0_P: J2.7, Module1.158 (HDMI1_TX0_P)
HDMI1_TX1_N: J2.6, Module1.154 (HDMI1_TX1_N)
HDMI1_TX1_P: J2.4, Module1.152 (HDMI1_TX1_P)
HDMI1_TX2_N: J2.3, Module1.148 (HDMI1_TX2_N)
HDMI1_TX2_P: J2.1, Module1.146 (HDMI1_TX2_P)
HSD1+: U3.7, U12.31
HSD1-: U3.6, U12.30
HSD2+: CN13.3, U3.9
HSD2-: CN13.2, U3.8
N00030: CN13.1, R75.2
N00031: Q2.1, R152.2, R154.2
N00041: U5.4, U12.18
N00048: C32.1, R52.2, U12.33, X3.1
N00049: C34.1, R52.1, U12.32, X3.2
N00060: U5.1, USB2.1
N00074: D2.1, R3.1
N00076: D1.1, R4.1
N00079: CN1a.1, R76.1, R77.1, U4.7
N00080: CN1a.2, R76.2, R78.2, U4.6
N00089: D17.2, R56.1
N00091: D16.2, R7.1
N00092: R83.1, T3.6
N00093: C96.2, R93.2
N00094: C93.1, R94.2
N00095: R96.2, U7.5
N00099: C20.1, CN15.1, CN15.6, CN15.7, CN15.12
N00100: D18.2, R9.2
NJ001: Rg.2, U10.1
NJ_cmp: R94.1, U9.3
NJ_en: Q2.3, R88.1, U9.6
NJ_g: Q5.3, Rg.1
NJ_rt: R95.1, U9.4
NJ_sw: L1.2, U9.8
NONrm0: R53.2, U12.28
Nj002: CS.2, RS.2, U10.2
Nj003: CnB.1, RnB.2
Nj005: CnB.2, CnF.2, Rn1.1, Rn2.2, U10.5
Nj007: Q5.4, RS.1, Rsen.2
Nj008: D8.1, L2.1, Q5.1, Q5.2, Q5.5, Q5.6
Nj009: RnF.1, U10.6
Nj010: CnF.1, RnF.2
Nj011: Ct.1, U10.7
Njen: Ren.2, U10.4
Nonrm: R55.1, U12.22
PCIe_CLK_N: Module1.110 (PCIe_CLK_P), U11.47 (REFCLKN_IN)
PCIe_CLK_P: Module1.112 (PCIe_CLK_N), U11.46 (REFCLKP_IN)
PCIe_CLK_nREQ: Module1.102 (PCIe_CLK_nREQ), R107.1, T1.52
PCIe_RX_N: Module1.118 (PCIe_RX_N), U11.54 (TXP_IN)
PCIe_RX_P: Module1.116 (PCIe_RX_P), U11.55 (TXN_IN)
PCIe_TX_N: Module1.124 (PCIe_TX_N), U11.51 (RXP_IN)
PCIe_TX_P: Module1.122 (PCIe_TX_P), U11.52 (RXN_IN)
PCIe_nRST: Module1.109 (PCIe_nRST), U11.3 (RES_IN)
PI_LED_nPWR: JP3.2, Module1.95 (nPI_LED_PWR)
PLLF: C43.1, U12.34
Pi_nLED_Activity: D17.1, Module1.21 (PI_nLED_Activity)
RBi: R54.1, U12.35
RSTO: CN5.4, T1.50, T2.52, T4.50, U11.2 (RES_OUT)
SCL0: CN4.4, CN4b.3, J5.13, Module1.80 (SCL0)
SDA0: CN4.3, CN4b.4, J5.14, Module1.82 (SDA0)
SD_CLK: J4.5, Module1.57 (SD_CLK)
SD_CMD: J4.3, Module1.62 (SD_CMD)
SD_DAT0: J4.7, Module1.63 (SD_DAT0)
SD_DAT1: J4.8, Module1.67 (SD_DAT1)
SD_DAT2: J4.1, Module1.69 (SD_DAT2)
SD_DAT3: J4.2, Module1.61 (SD_DAT3)
SD_PWR: J4.4, U7.6
SD_PWR_ON: Module1.75 (SD_PWR_ON), R97.1, U7.3
SIM_DATE: C86.1, J15.C7, T3.34
SIM_PWR: C83.1, J15.C1, T3.36
SIM_RST: C84.1, J15.C2, T3.30
SIM_SLK: C85.1, J15.C3, T3.32
SIM_SW: R82.2, T3.60
USB1+: T3.7, U12.2
USB1-: T3.9, U12.1
USB2+: T2.3, U12.4
USB2-: T2.5, U12.3
USB3+: U12.7, USB2.3
USB3-: U12.6, USB2.2
USB4+: R105x.1, U12.9
USB4-: R106x.1, U12.8
USBD5+: CN4.21, CN4b.16, R105x.2
USBD5-: CN4.20, CN4b.15, R106x.2
USB_N: Module1.103 (USB2_N), U3.4
USB_OTG_ID: Module1.101 (USB_OTG_ID), R74.2, R75.1, U3.2
USB_P: Module1.105 (USB2_P), U3.3
VCC: CP7.1, Module1.84 (+3.3v_(Output)), Module1.86 (+3.3v_(Output)), R97.2, R100.1, U7.1
VCC-2: C95.2, CN17.1, CP4.1, CS.1, D1.2, D2.2, IC1.1, IC1.2, Module1.77 (+5v_(Input)), Module1.79 (+5v_(Input)), Module1.81 (+5v_(Input)), Module1.83 (+5v_(Input)), Module1.85 (+5v_(Input)), Module1.87 (+5v_(Input)), Q1.1, Q1.2, Q1.5, Q1.6, R77.2, R88.2, Ravin.2, Ren.1, Rsen.1, U5.5, U6.3, U9.1, U10.3, pg.2
WLANEN: R85.2, T2.56
WL_nDisable: JP1.2, Module1.89 (WL_nDisable)
WWAN_LED: D18.1, T3.10
fclk1+: T4.53, U11.18 (REFCLKP_1)
fclk1-: T4.55, U11.19 (REFCLKN_1)
fclk2+: CN5.2, U11.27 (REFCLKP_2)
fclk2-: CN5.3, U11.28 (REFCLKN_2)
fclk3+: T1.55, U11.44 (REFCLKP_3)
fclk3-: T1.53, U11.45 (REFCLKN_3)
fclk4+: T2.47, U11.62 (REFCLKP_4)
fclk4-: T2.49, U11.63 (REFCLKN_4)
h003: R33.2, U11.4 (GPIO_0)
h004: R23.1, U11.5 (GPIO_2)
h005: R22.1, U11.8 (GPIO_4)
h012: R30.1, U11.16 (REXT1)
h025: R26.2, U11.30 (GPIO_5)
h026: R24.2, U11.31 (GPIO_1)
h027: R27.1, U11.33 (TEST_EN)
h028: R29.2, U11.34 (GPIO_3)
h029: R25.1, U11.35 (GPIO_6)
h030: R28.2, U11.36 (GPIO_7)
m002: Cavin.2, IC1.3, IC1.5, Ravin.1
m003: IC1.4, pg.1
m3das: D19.1, T1.10
m004: Css.2, IC1.6
m005: C11.1, IC1.7, R1.1, R2.2
m006: IC1.11, IC1.12, L11.1
nEXTRST: Module1.100 (nEXTRST), U12.26
nRPIBOOT: JP5.2, Module1.93 (nRPIBOOT)
rext2: R36.1, U11.49 (REXT2)
rx1+: T4.41, U11.13 (RXP_1)
rx1-: T4.43, U11.14 (RXN_1)
rx2+: CN5.9, U11.24 (RXP_2)
rx2-: CN5.8, U11.25 (RXN_2)
rx3+: T1.43, U11.41 (RXP_3)
rx3-: T1.41, U11.42 (RXN_3)
rx4+: T2.41, U11.59 (RXP_4)
rx4-: T2.43, U11.60 (RXN_4)
tx1+: C52.2, U11.11 (TXP_1)
tx1-: C53.2, U11.12 (TXN_1)
tx1c+: C52.1, T4.47
tx1c-: C53.1, T4.49
tx2+: C54.2, U11.22 (TXP_2)
tx2-: C55.2, U11.23 (TXN_2)
tx2c+: C54.1, CN5.6
tx2c-: C55.1, CN5.5
tx3+: C56.2, U11.39 (TXP_3)
tx3-: C57.2, U11.40 (TXN_3)
tx3c+: C56.1, T1.49
tx3c-: C57.1, T1.47
tx4+: C58.2, U11.57 (TXP_4)
tx4-: C59.2, U11.58 (TXN_4)
tx4c+: C58.1, T2.35
tx4c-: C59.1, T2.37

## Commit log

2024-12-28 Add files via upload
    回路図をupしました
2024-12-28 Create iperf3_speedtest
2024-12-28 Update README.md
    boot CM5 via NVMe behind PCIe switch
